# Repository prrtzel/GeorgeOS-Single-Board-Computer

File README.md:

# GeorgeOS Single Board Computer

This was the final project for the Microcomputer Design Course at LeTourneau University.

Software for this project can be found here: [Morg Monitor Program](https://github.com/prrtzel/Morg-Monitor-Program)

The schematic and PCB designs can be viewed in detail using the 
[Kicanvas Online Viewer](https://kicanvas.org/?github=https%3A%2F%2Fgithub.com%2Fprrtzel%2FGeorgeOS-Single-Board-Computer%2Ftree%2Fmain%2FHardware%2FKiCAD)

The requirements for the project were as follows:

- Read from memory
- Write to memory
- Read from registers
- Write to registers
- Load an S-Record file
- Jump to the S-Record file and run it

## Schematic

## Printed Circuit Board

## Assembled Board

## Hardware Specifications
- Motorola 68000 32-bit CPU with an 8MHz clock speed
- Xilinx XC9572XL CPLD for address decoding / glue logic
- Dual channel UART interface for serial communication

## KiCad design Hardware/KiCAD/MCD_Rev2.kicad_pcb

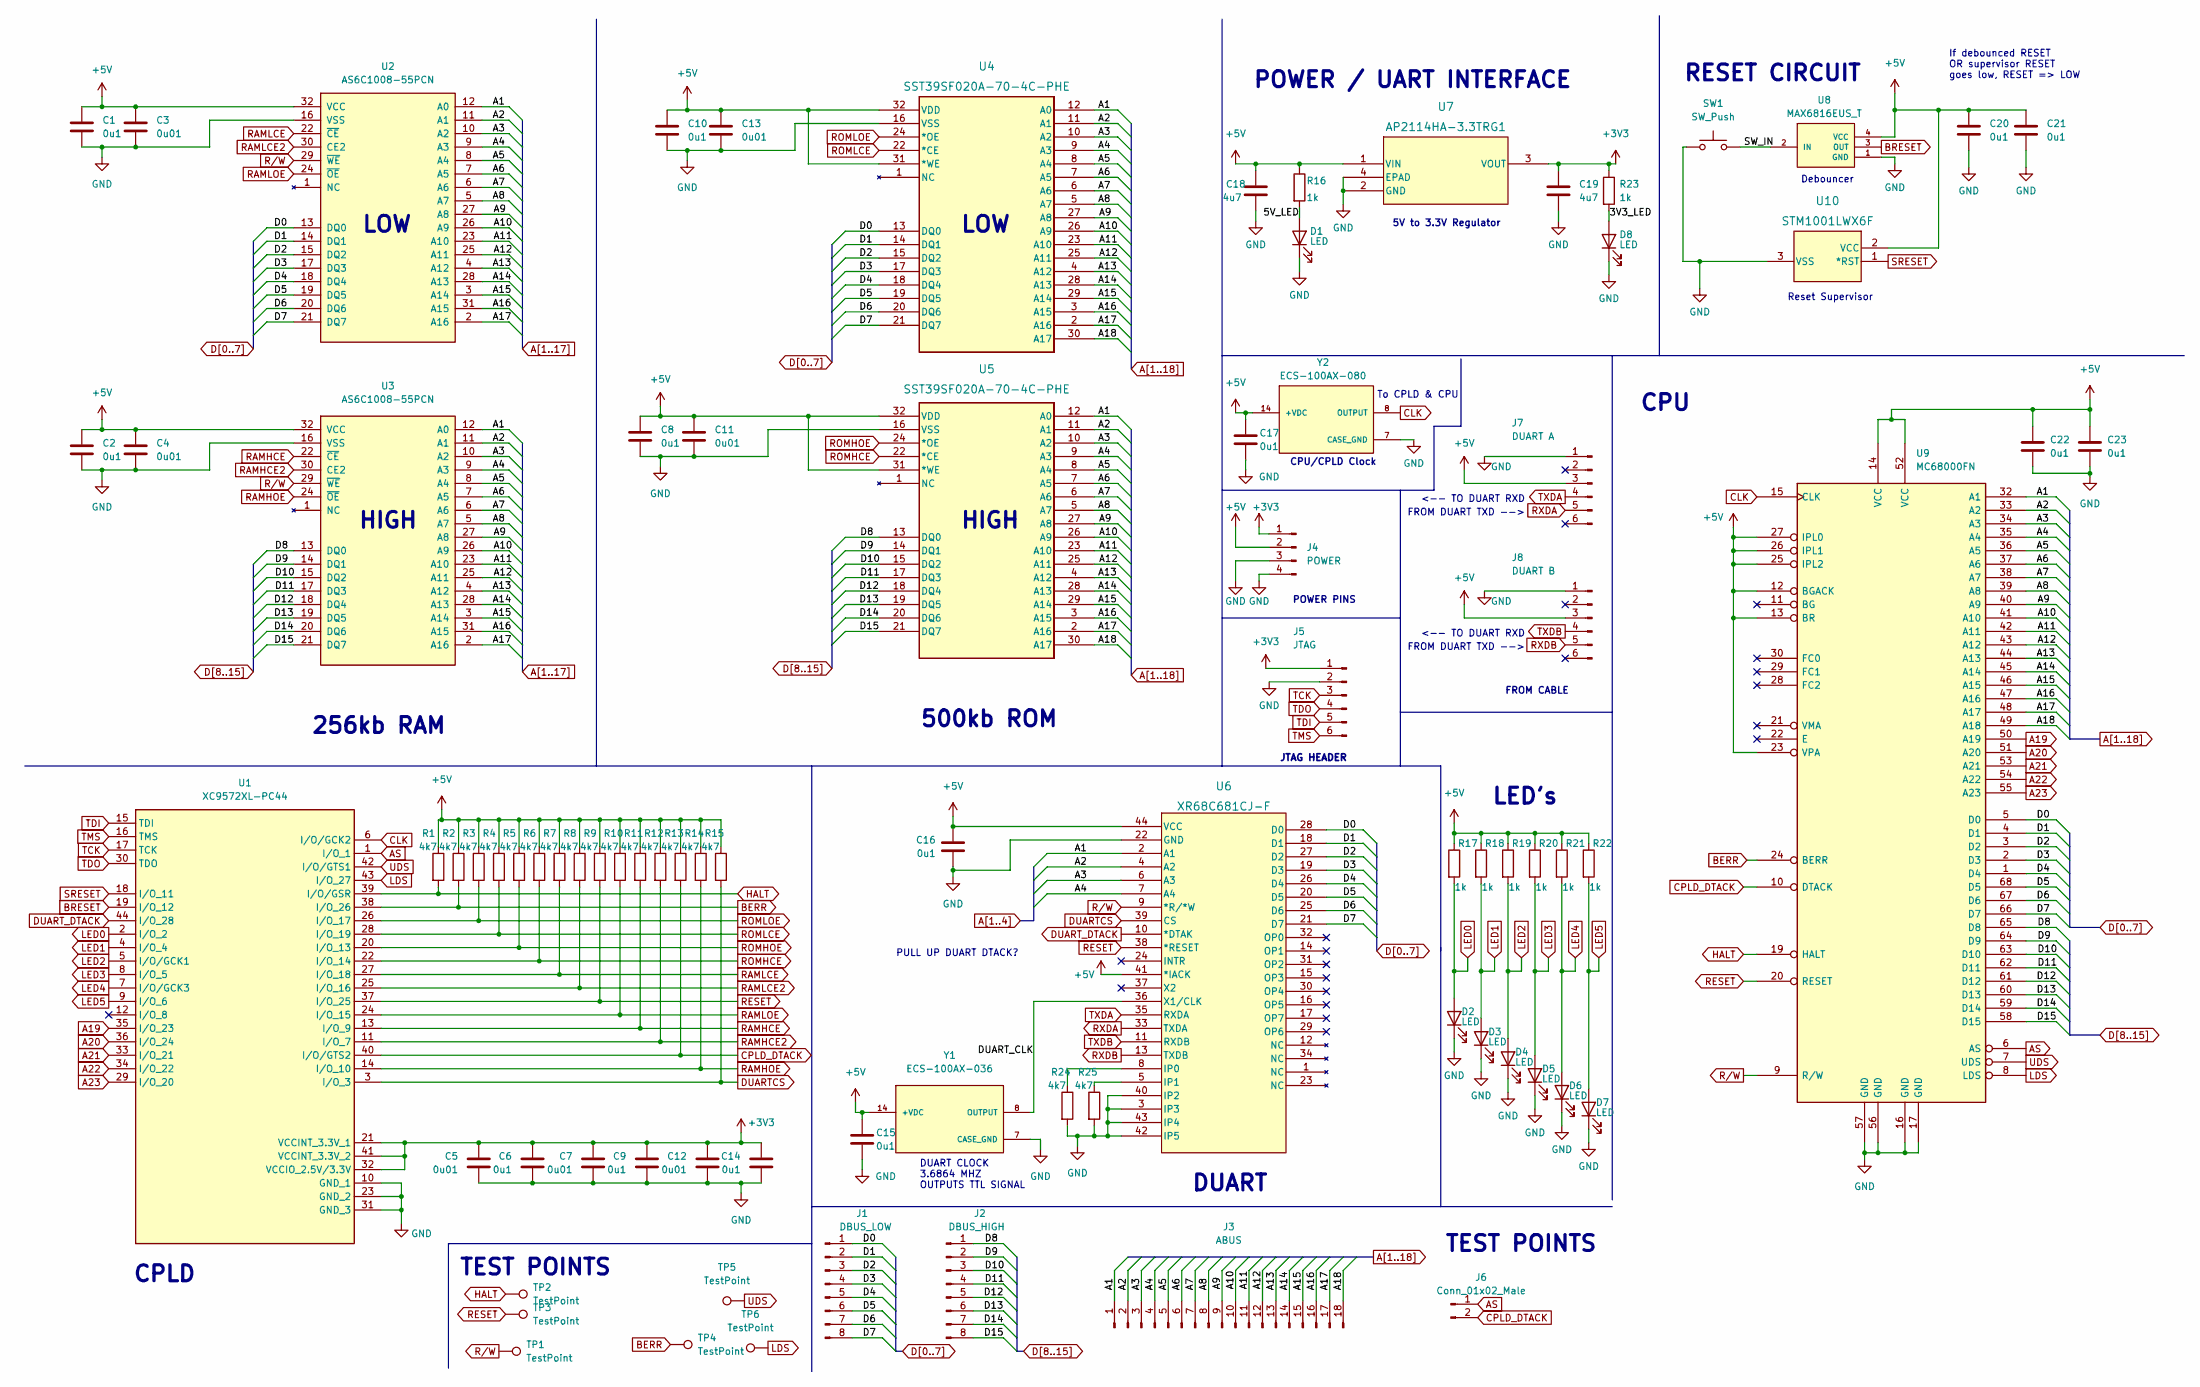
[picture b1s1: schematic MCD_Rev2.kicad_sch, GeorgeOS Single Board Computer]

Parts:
C1, C2, C6, C8, C9, C10, C14, C15, C16, C17, C20, C21, C22, C23: 0u1; C_0805_2012Metric_Pad1.18x1.45mm_HandSolder
C3, C4, C5, C7, C11, C12, C13: 0u01; C_0805_2012Metric_Pad1.18x1.45mm_HandSolder
C18, C19: 4u7; C_0805_2012Metric_Pad1.18x1.45mm_HandSolder
D1, D2, D3, D4, D5, D6, D7, D8: LED; LED_0805_2012Metric_Pad1.15x1.40mm_HandSolder
J1: DBUS_LOW; CON8_1X8_TU_HTS_SAI
J2: DBUS_HIGH; CON8_1X8_TU_HTS_SAI
J3: ABUS; CON18_2X9_TU_HTS_SAI
J4: POWER; CON4_1X4_TU_HTS_SAI
J5: JTAG; CON6_1X6_TU_HTS_SAI
J6: Conn_01x02_Male; CON2_1X2_TU_HTS_SAI
J7: DUART A; CON6_1X6_TU_HTS_SAI
J8: DUART B; CON6_1X6_TU_HTS_SAI
R1, R2, R3, R4, R5, R6, R7, R8, R9, R10, R11, R12, R13, R14, R15, R24, R25: 4k7; R_0805_2012Metric_Pad1.20x1.40mm_HandSolder
R16, R17, R18, R19, R20, R21, R22, R23: 1k; R_0805_2012Metric_Pad1.20x1.40mm_HandSolder
SW1: SW_Push; SW_PUSH_6mm
TP1, TP2, TP3, TP4, TP5, TP6: TestPoint; TestPoint_Pad_D1.0mm
U1: XC9572XL-PC44; TO_11B1-RK-TP_3MM
U2, U3: AS6C1008-55PCN; PDIP32_PH_SST_MCH; PARTREV v1.0
U4, U5: SST39SF020A-70-4C-PHE; PDIP32_PH_SST_MCH
U6: XR68C681CJ-F; TO_11B1-RK-TP_3MM
U7: AP2114HA-3.3TRG1; SOT-223_DIO-L
U8: MAX6816EUS_T; SOT-143_Handsoldering
U9: MC68000FN; 3M_8468-11B1-RK-TP
U10: STM1001LWX6F; SOT-23_STM-L
Y1: ECS-100AX-036; OSC_ECS-100AX-036
Y2: ECS-100AX-080; OSC_ECS-100AX-080

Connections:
+3V3: C5.1, C6.1, C7.1, C9.1, C12.1, C14.1, C19.1, J4.1, J5.1, R23.1, U1.21 (VCCINT_3.3V_1), U1.32 (VCCIO_2.5V/3.3V), U1.41 (VCCINT_3.3V_2), U7.3 (VOUT)
+5V: C1.1, C2.1, C3.1, C4.1, C8.1, C10.1, C11.1, C13.1, C15.1, C16.1, C17.1, C18.1, C20.1, C21.1, C22.1, C23.1, J4.2, J7.3, J8.3, R1.1, R2.1, R3.1, R4.1, R5.1, R6.1, R7.1, R8.1, R9.1, R10.1, R11.1, R12.1, R13.1, R14.1, R15.1, R16.1, R17.1, R18.1, R19.1, R20.1, R21.1, R22.1, U2.32 (VCC), U3.32 (VCC), U4.31 (*WE), U4.32 (VDD), U5.31 (*WE), U5.32 (VDD), U6.41 (*IACK), U6.44 (VCC), U7.1 (VIN), U8.4 (VCC), U9.12 (BGACK), U9.13 (BR), U9.14 (VCC), U9.23 (VPA), U9.25 (IPL2), U9.26 (IPL1), U9.27 (IPL0), U9.52 (VCC), U10.2 (VCC), Y1.14 (+VDC), Y2.14 (+VDC)
/3V3_LED: D8.2 (A), R23.2
/5V_LED: D1.2 (A), R16.2
/DUART_CLK: U6.36 (X1/CLK), Y1.8 (OUTPUT)
/SW_IN: SW1.2, U8.2 (IN)
A1: J3.1, U2.12 (A0), U3.12 (A0), U4.12 (A0), U5.12 (A0), U6.2 (A1), U9.32 (A1)
A2: J3.2, U2.11 (A1), U3.11 (A1), U4.11 (A1), U5.11 (A1), U6.4 (A2), U9.33 (A2)
A3: J3.3, U2.10 (A2), U3.10 (A2), U4.10 (A2), U5.10 (A2), U6.6 (A3), U9.34 (A3)
A4: J3.4, U2.9 (A3), U3.9 (A3), U4.9 (A3), U5.9 (A3), U6.7 (A4), U9.35 (A4)
A5: J3.5, U2.8 (A4), U3.8 (A4), U4.8 (A4), U5.8 (A4), U9.36 (A5)
A6: J3.6, U2.7 (A5), U3.7 (A5), U4.7 (A5), U5.7 (A5), U9.37 (A6)
A7: J3.7, U2.6 (A6), U3.6 (A6), U4.6 (A6), U5.6 (A6), U9.38 (A7)
A8: J3.8, U2.5 (A7), U3.5 (A7), U4.5 (A7), U5.5 (A7), U9.39 (A8)
A9: J3.9, U2.27 (A8), U3.27 (A8), U4.27 (A8), U5.27 (A8), U9.40 (A9)
A10: J3.10, U2.26 (A9), U3.26 (A9), U4.26 (A9), U5.26 (A9), U9.41 (A10)
A11: J3.11, U2.23 (A10), U3.23 (A10), U4.23 (A10), U5.23 (A10), U9.42 (A11)
A12: J3.12, U2.25 (A11), U3.25 (A11), U4.25 (A11), U5.25 (A11), U9.43 (A12)
A13: J3.13, U2.4 (A12), U3.4 (A12), U4.4 (A12), U5.4 (A12), U9.44 (A13)
A14: J3.14, U2.28 (A13), U3.28 (A13), U4.28 (A13), U5.28 (A13), U9.45 (A14)
A15: J3.15, U2.3 (A14), U3.3 (A14), U4.29 (A14), U5.29 (A14), U9.46 (A15)
A16: J3.16, U2.31 (A15), U3.31 (A15), U4.3 (A15), U5.3 (A15), U9.47 (A16)
A17: J3.17, U2.2 (A16), U3.2 (A16), U4.2 (A16), U5.2 (A16), U9.48 (A17)
A18: J3.18, U4.30 (A17), U5.30 (A17), U9.49 (A18)
A19: U1.35 (I/O_23), U9.50 (A19)
A20: U1.36 (I/O_24), U9.51 (A20)
A21: U1.33 (I/O_21), U9.53 (A21)
A22: U1.34 (I/O_22), U9.54 (A22)
A23: U1.29 (I/O_20), U9.55 (A23)
AS: J6.1, U1.1 (I/O_1), U9.6 (AS)
BERR: R2.2, TP4.1, U1.38 (I/O_26), U9.24 (BERR); also elsewhere on the board
BRESET: U1.19 (I/O_12), U8.3 (OUT)
CLK: U1.6 (I/O/GCK2), U9.15 (CLK), Y2.8 (OUTPUT)
CPLD_DTACK: J6.2, R13.2, U1.40 (I/O/GTS2), U9.10 (DTACK)
D0: J1.1, U2.13 (DQ0), U4.13 (DQ0), U6.28 (D0), U9.5 (D0)
D1: J1.2, U2.14 (DQ1), U4.14 (DQ1), U6.18 (D1), U9.4 (D1)
D2: J1.3, U2.15 (DQ2), U4.15 (DQ2), U6.27 (D2), U9.3 (D2)
D3: J1.4, U2.17 (DQ3), U4.17 (DQ3), U6.19 (D3), U9.2 (D3)
D4: J1.5, U2.18 (DQ4), U4.18 (DQ4), U6.26 (D4), U9.1 (D4)
D5: J1.6, U2.19 (DQ5), U4.19 (DQ5), U6.20 (D5), U9.68 (D5)
D6: J1.7, U2.20 (DQ6), U4.20 (DQ6), U6.25 (D6), U9.67 (D6)
D7: J1.8, U2.21 (DQ7), U4.21 (DQ7), U6.21 (D7), U9.66 (D7)
D8: J2.1, U3.13 (DQ0), U5.13 (DQ0), U9.65 (D8)
D9: J2.2, U3.14 (DQ1), U5.14 (DQ1), U9.64 (D9)
D10: J2.3, U3.15 (DQ2), U5.15 (DQ2), U9.63 (D10)
D11: J2.4, U3.17 (DQ3), U5.17 (DQ3), U9.62 (D11)
D12: J2.5, U3.18 (DQ4), U5.18 (DQ4), U9.61 (D12)
D13: J2.6, U3.19 (DQ5), U5.19 (DQ5), U9.60 (D13)
D14: J2.7, U3.20 (DQ6), U5.20 (DQ6), U9.59 (D14)
D15: J2.8, U3.21 (DQ7), U5.21 (DQ7), U9.58 (D15)
DUARTCS: R15.2, U1.3 (I/O_3), U6.39 (CS)
DUART_DTACK: U1.44 (I/O_28), U6.10 (*DTAK)
GND: C1.2, C2.2, C3.2, C4.2, C5.2, C6.2, C7.2, C8.2, C9.2, C10.2, C11.2, C12.2, C13.2, C14.2, C15.2, C16.2, C17.2, C18.2, C19.2, C20.2, C21.2, C22.2, C23.2, D1.1 (K), D2.1 (K), D3.1 (K), D4.1 (K), D5.1 (K), D6.1 (K), D7.1 (K), D8.1 (K), J4.3, J4.4, J5.2, J7.1, J8.1, R24.2, R25.2, SW1.1, U1.10 (GND_1), U1.23 (GND_2), U1.31 (GND_3), U2.16 (VSS), U3.16 (VSS), U4.16 (VSS), U5.16 (VSS), U6.3 (IP3), U6.22 (GND), U6.40 (IP2), U6.42 (IP5), U6.43 (IP4), U7.2 (GND), U7.4 (EPAD), U8.1 (GND), U9.16 (GND), U9.17 (GND), U9.56 (GND), U9.57 (GND), U10.3 (VSS), Y1.7 (CASE_GND), Y2.7 (CASE_GND)
HALT: R1.2, TP2.1, U1.39 (I/O/GSR), U9.19 (HALT); also elsewhere on the board
LDS: TP6.1, U1.43 (I/O_27), U9.8 (LDS); also elsewhere on the board
LED0: D2.2 (A), R17.2, U1.2 (I/O_2)
LED1: D3.2 (A), R18.2, U1.4 (I/O_4)
LED2: D4.2 (A), R19.2, U1.5 (I/O/GCK1)
LED3: D5.2 (A), R20.2, U1.8 (I/O_5)
LED4: D6.2 (A), R21.2, U1.7 (I/O/GCK3)
LED5: D7.2 (A), R22.2, U1.9 (I/O_6)
unnamed: R24.1, U6.8 (IP0)
unnamed: R25.1, U6.5 (IP1)
RAMHCE: R11.2, U1.13 (I/O_9), U3.22 (~CE)
RAMHCE2: R12.2, U1.11 (I/O_7), U3.30 (CE2)
RAMHOE: R14.2, U1.14 (I/O_10), U3.24 (~OE)
RAMLCE: R7.2, U1.27 (I/O_18), U2.22 (~CE)
RAMLCE2: R8.2, U1.25 (I/O_16), U2.30 (CE2)
RAMLOE: R10.2, U1.24 (I/O_15), U2.24 (~OE)
RESET: R9.2, TP3.1, U1.37 (I/O_25), U6.38 (*RESET), U9.20 (RESET); also elsewhere on the board
ROMHCE: R6.2, U1.22 (I/O_14), U5.22 (*CE)
ROMHOE: R5.2, U1.20 (I/O_13), U5.24 (*OE)
ROMLCE: R4.2, U1.28 (I/O_19), U4.22 (*CE)
ROMLOE: R3.2, U1.26 (I/O_17), U4.24 (*OE)
RXDA: J7.5, U6.33 (TXDA)
RXDB: J8.5, U6.13 (TXDB)
R/W: TP1.1, U2.29 (~WE), U3.29 (~WE), U6.9 (*R/*W), U9.9 (R/W); also elsewhere on the board
SRESET: U1.18 (I/O_11), U10.1 (*RST)
TCK: J5.3, U1.17 (TCK)
TDI: J5.5, U1.15 (TDI)
TDO: J5.4, U1.30 (TDO)
TMS: J5.6, U1.16 (TMS)
TXDA: J7.4, U6.35 (RXDA)
TXDB: J8.4, U6.11 (RXDB)
UDS: TP5.1, U1.42 (I/O/GTS1), U9.7 (UDS); also elsewhere on the board

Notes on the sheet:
LOW
DUART
<-- TO DUART RXD
FROM DUART TXD -->
CPLD
To CPLD & CPU
256kb RAM
Debouncer
CPU/CPLD Clock
HIGH
JTAG HEADER
TEST POINTS
PULL UP DUART DTACK?
DUART CLOCK 3.6864 MHZ OUTPUTS TTL SIGNAL
POWER PINS
TEST POINTS
LED's
FROM CABLE
HIGH
5V to 3.3V Regulator
RESET CIRCUIT
Reset Supervisor
POWER / UART INTERFACE
If debounced RESET OR supervisor RESET goes low, RESET => LOW
CPU
500kb ROM

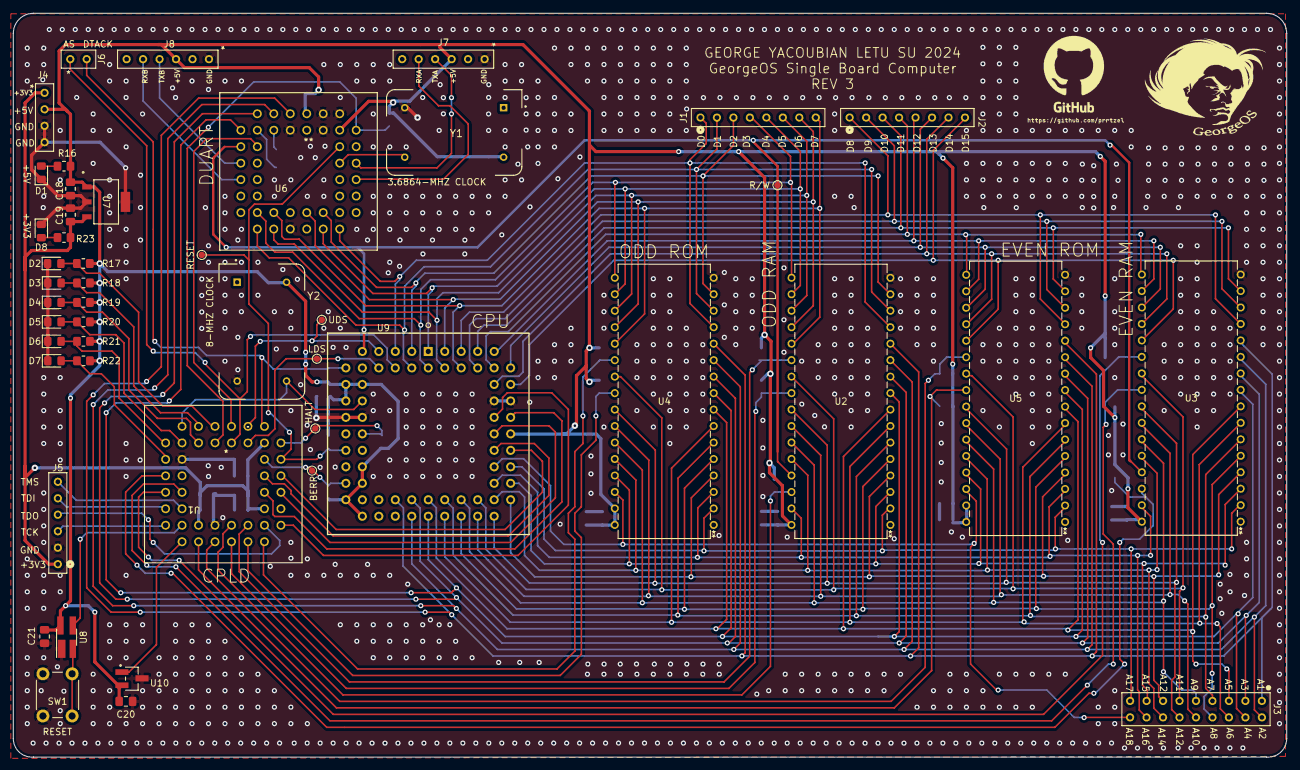
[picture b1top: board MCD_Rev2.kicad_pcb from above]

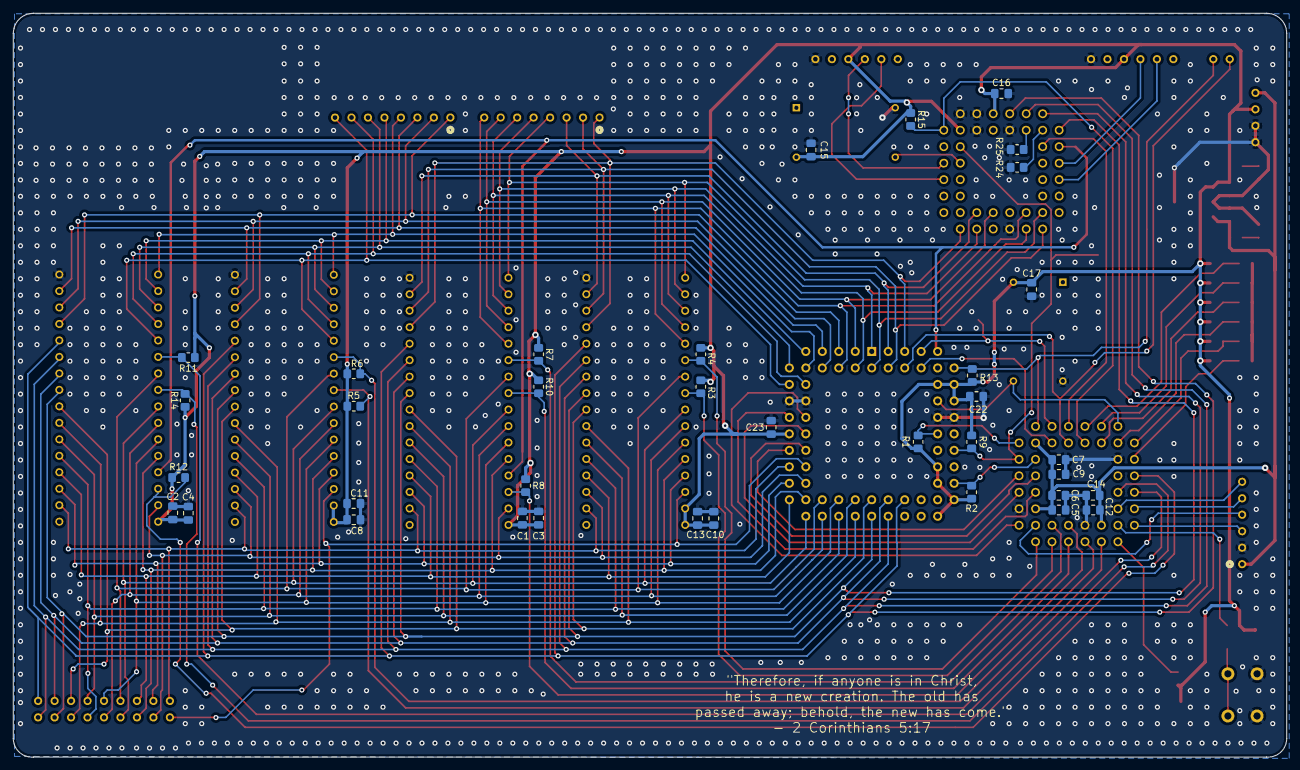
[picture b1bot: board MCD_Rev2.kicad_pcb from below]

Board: 2 copper layers, 196.3 x 114.7 mm, 83 parts (36 on the bottom side), 85 nets.

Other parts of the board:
BERR: TestPoint; TestPoint_Pad_D1.0mm
HALT: TestPoint; TestPoint_Pad_D1.0mm
LDS: TestPoint; TestPoint_Pad_D1.0mm
R/W: TestPoint; TestPoint_Pad_D1.0mm
RESET: TestPoint; TestPoint_Pad_D1.0mm
UDS: TestPoint; TestPoint_Pad_D1.0mm

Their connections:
BERR: BERR.1; also elsewhere on the board
HALT: HALT.1; also elsewhere on the board
LDS: LDS.1; also elsewhere on the board
RESET: RESET.1; also elsewhere on the board
R/W: R/W.1; also elsewhere on the board
UDS: UDS.1; also elsewhere on the board

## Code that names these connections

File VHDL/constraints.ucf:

NET SRESET	    LOC=P18;
NET BRESET	    LOC=P19;
NET DUART_DTACK LOC=P44;
NET HALT        LOC=P39;
NET BERR        LOC=P38;
NET RESET       LOC=P37;
NET CPU_DTACK   LOC=P40;
NET DUARTCS     LOC=P3;

NET ABUS<0>	    LOC=P35;
NET ABUS<1>	    LOC=P36;

NET LED<0>	    LOC=P2;
NET LED<1>	    LOC=P4;
NET LED<2>	    LOC=P5;
NET LED<3>	    LOC=P8;
NET LED<4>	    LOC=P7;
NET LED<5>	    LOC=P9;

NET CLK         LOC=P6;
NET AS          LOC=P1;
NET UDS         LOC=P42;
NET LDS         LOC=p43;

NET ROMLOE      LOC=P26;
NET ROMLCE      LOC=P28;

NET ROMHOE      LOC=P20;
NET ROMHCE      LOC=P22;

NET RAMLCE      LOC=P27;
NET RAMLCE2     LOC=P25;
NET RAMLOE      LOC=P24;

NET RAMHCE      LOC=P13;
NET RAMHCE2     LOC=P11;
NET RAMHOE      LOC=P14;

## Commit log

2024-11-20 fixed schematic picture not showing up
2024-11-20 Added Files
2024-11-20 added GeorgeOS Logo
2024-11-20 updated logo size
2024-11-20 .vs eliminated
